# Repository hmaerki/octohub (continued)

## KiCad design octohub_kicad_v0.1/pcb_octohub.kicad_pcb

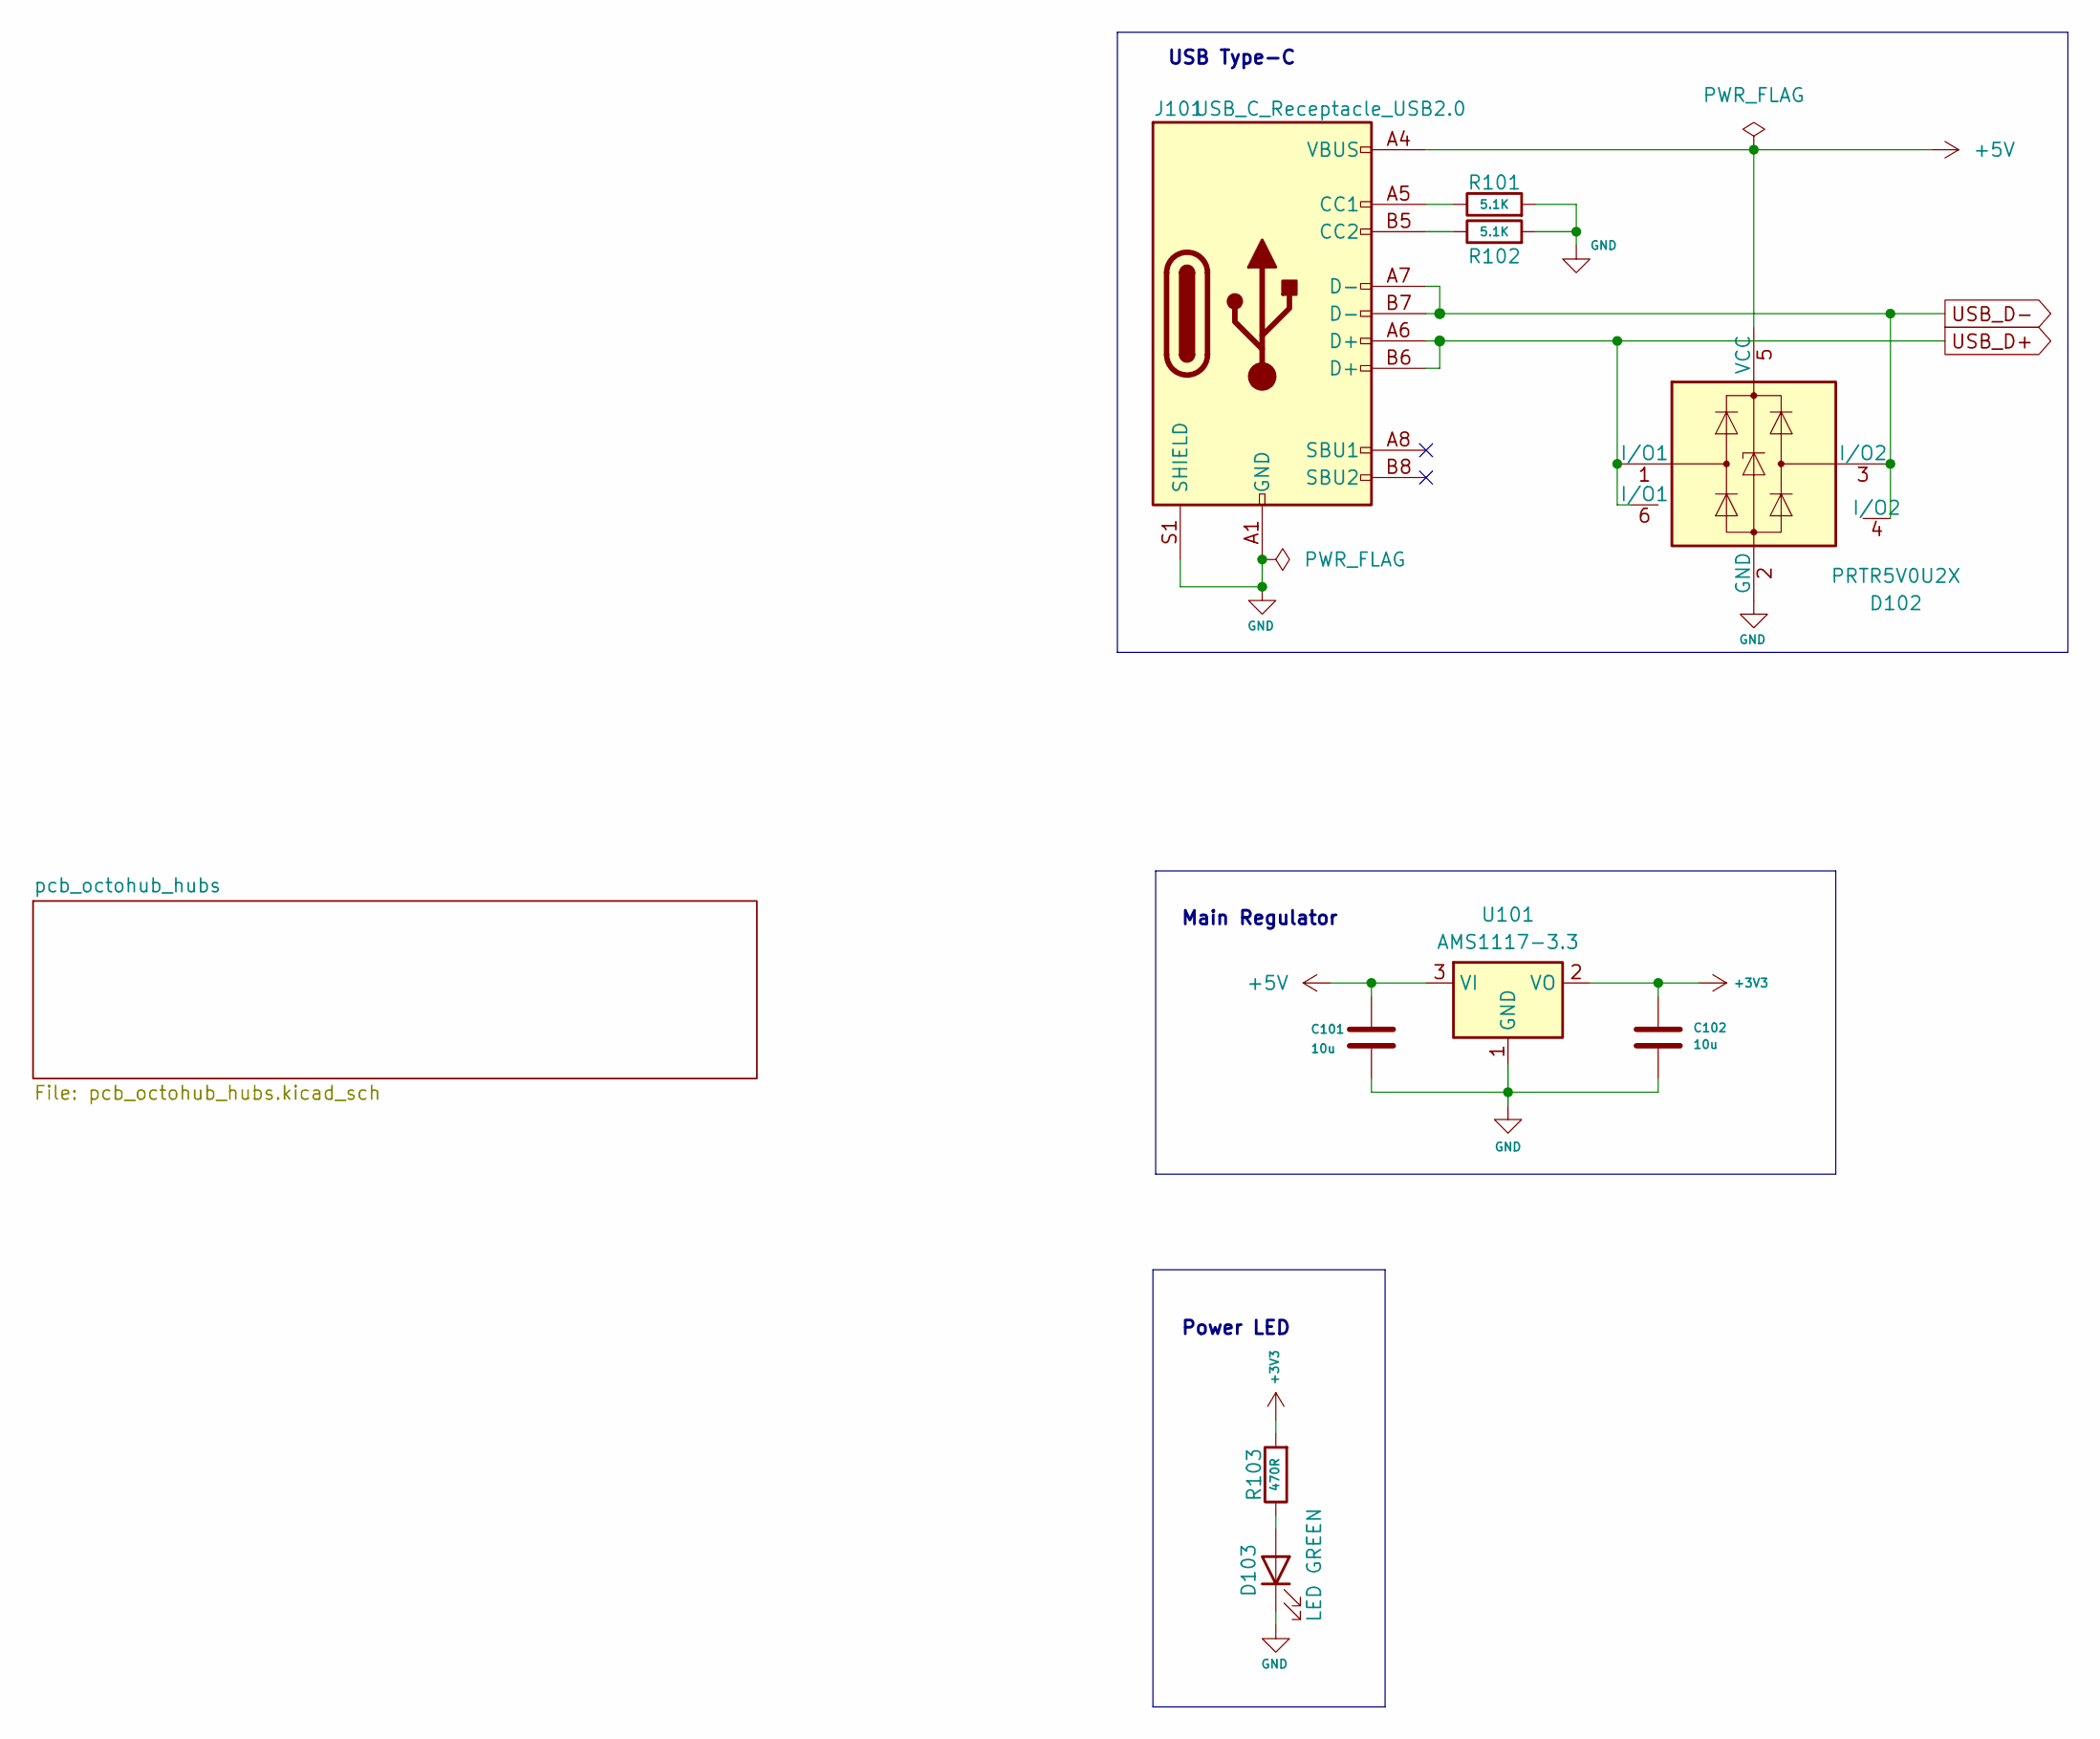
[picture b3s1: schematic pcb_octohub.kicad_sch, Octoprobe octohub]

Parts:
C101, C102: 10u; C_0603_1608Metric
D102: PRTR5V0U2X; Texas_USON-6_1x1.45mm_P0.5mm_SMD; JLC C2937001
D103: LED GREEN; LED_0603_1608Metric; JLC C2297
J101: USB_C_Receptacle_USB2.0; USB_C_Receptacle_Palconn_UTC16-G; JLC C165948
R101, R102: 5.1K; R_0402_1005Metric_Pad0.72x0.64mm_HandSolder
R103: 470R; R_0402_1005Metric_Pad0.72x0.64mm_HandSolder
U101: AMS1117-3.3; SOT-223-3_TabPin2; JLC C6186

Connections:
+3V3: C102.1, R103.2, U101.2 (VO); also elsewhere on the board
+5V: C101.1, D102.5 (VCC), J101.A4 (VBUS), J101.A9 (VBUS), J101.B4 (VBUS), J101.B9 (VBUS), U101.3 (VI); also elsewhere on the board
GND: C101.2, C102.2, D102.2 (GND), D103.1 (K), J101.A1 (GND), J101.A12 (GND), J101.B1 (GND), J101.B12 (GND), J101.S1 (SHIELD), R101.2, R102.2, U101.1 (GND); also elsewhere on the board
unnamed: D103.2 (A), R103.1
unnamed: J101.A5 (CC1), R101.1
unnamed: J101.B5 (CC2), R102.1
USB_D+: D102.1 (I/O1), D102.6 (I/O1), J101.A6 (D+), J101.B6 (D+); also elsewhere on the board
USB_D-: D102.3 (I/O2), D102.4 (I/O2), J101.A7 (D-), J101.B7 (D-); also elsewhere on the board

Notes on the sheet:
USB Type-C
Power LED
Main Regulator

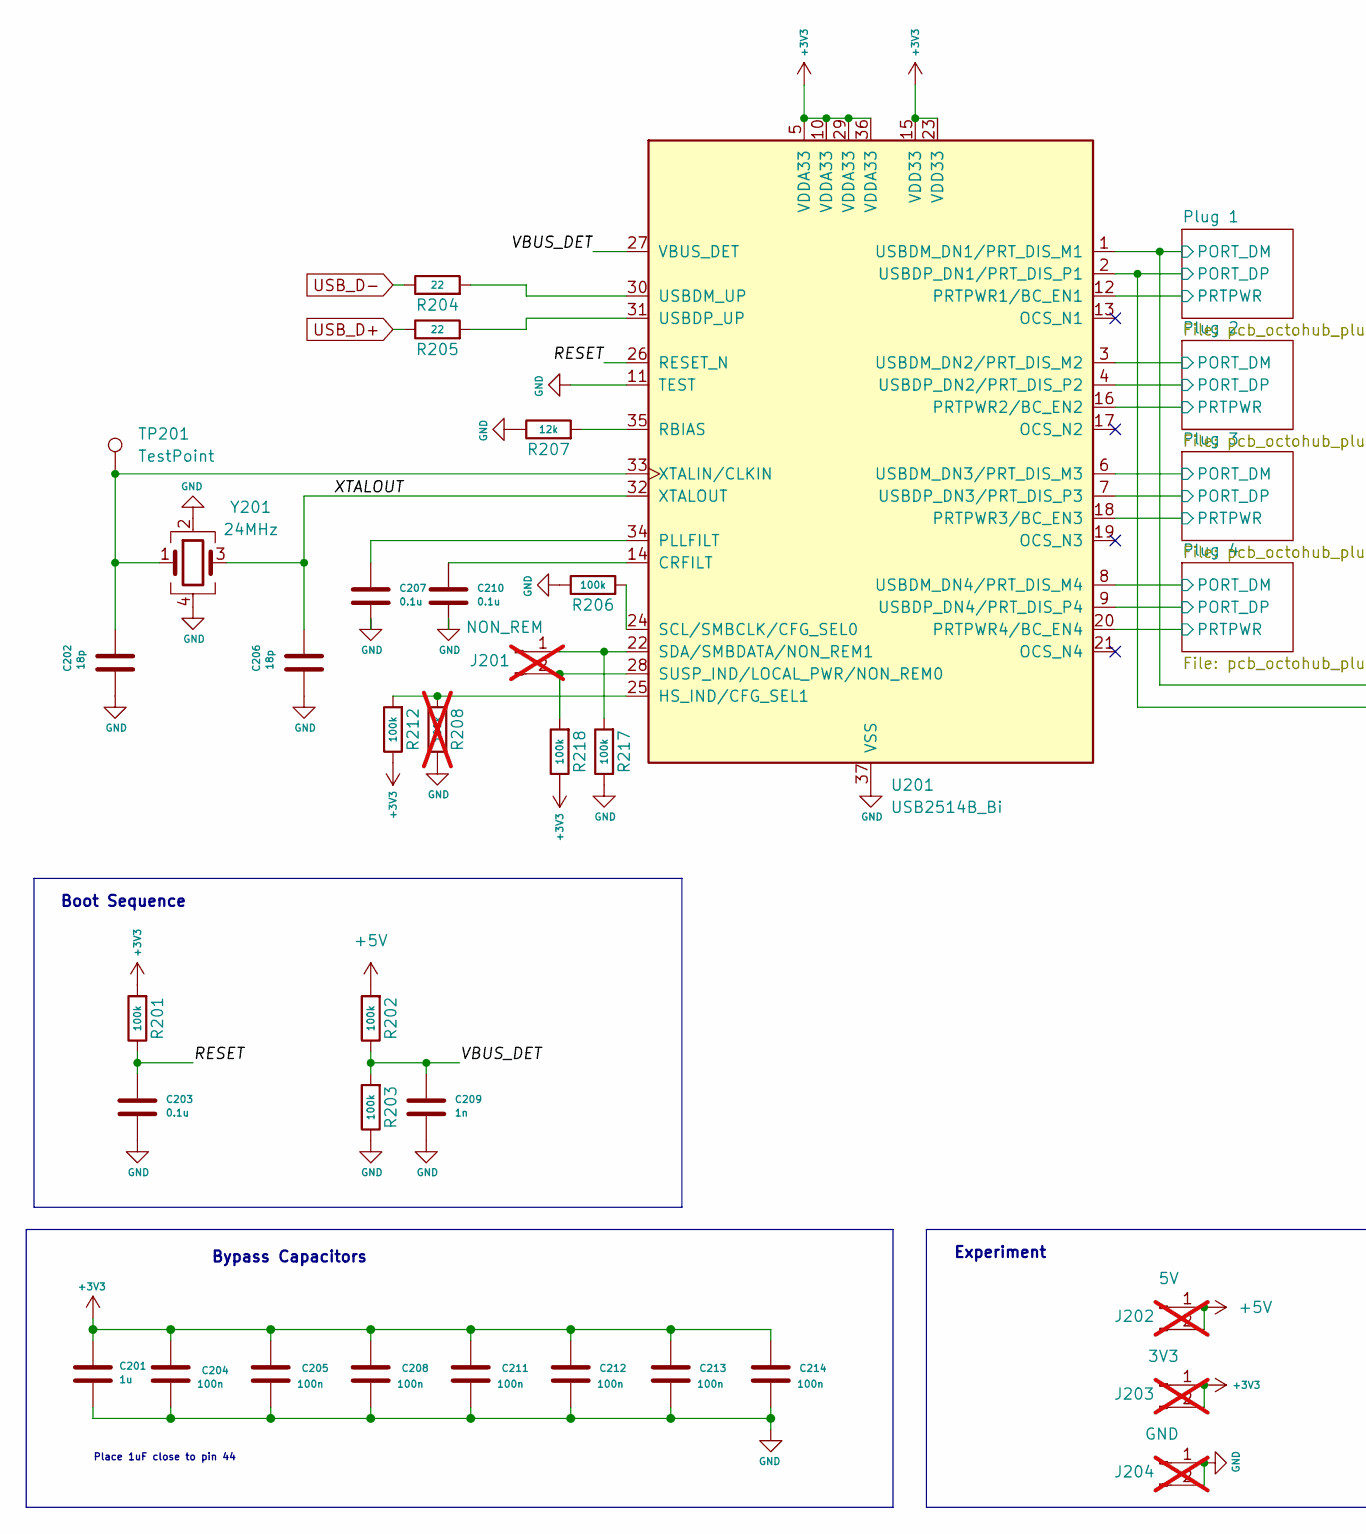
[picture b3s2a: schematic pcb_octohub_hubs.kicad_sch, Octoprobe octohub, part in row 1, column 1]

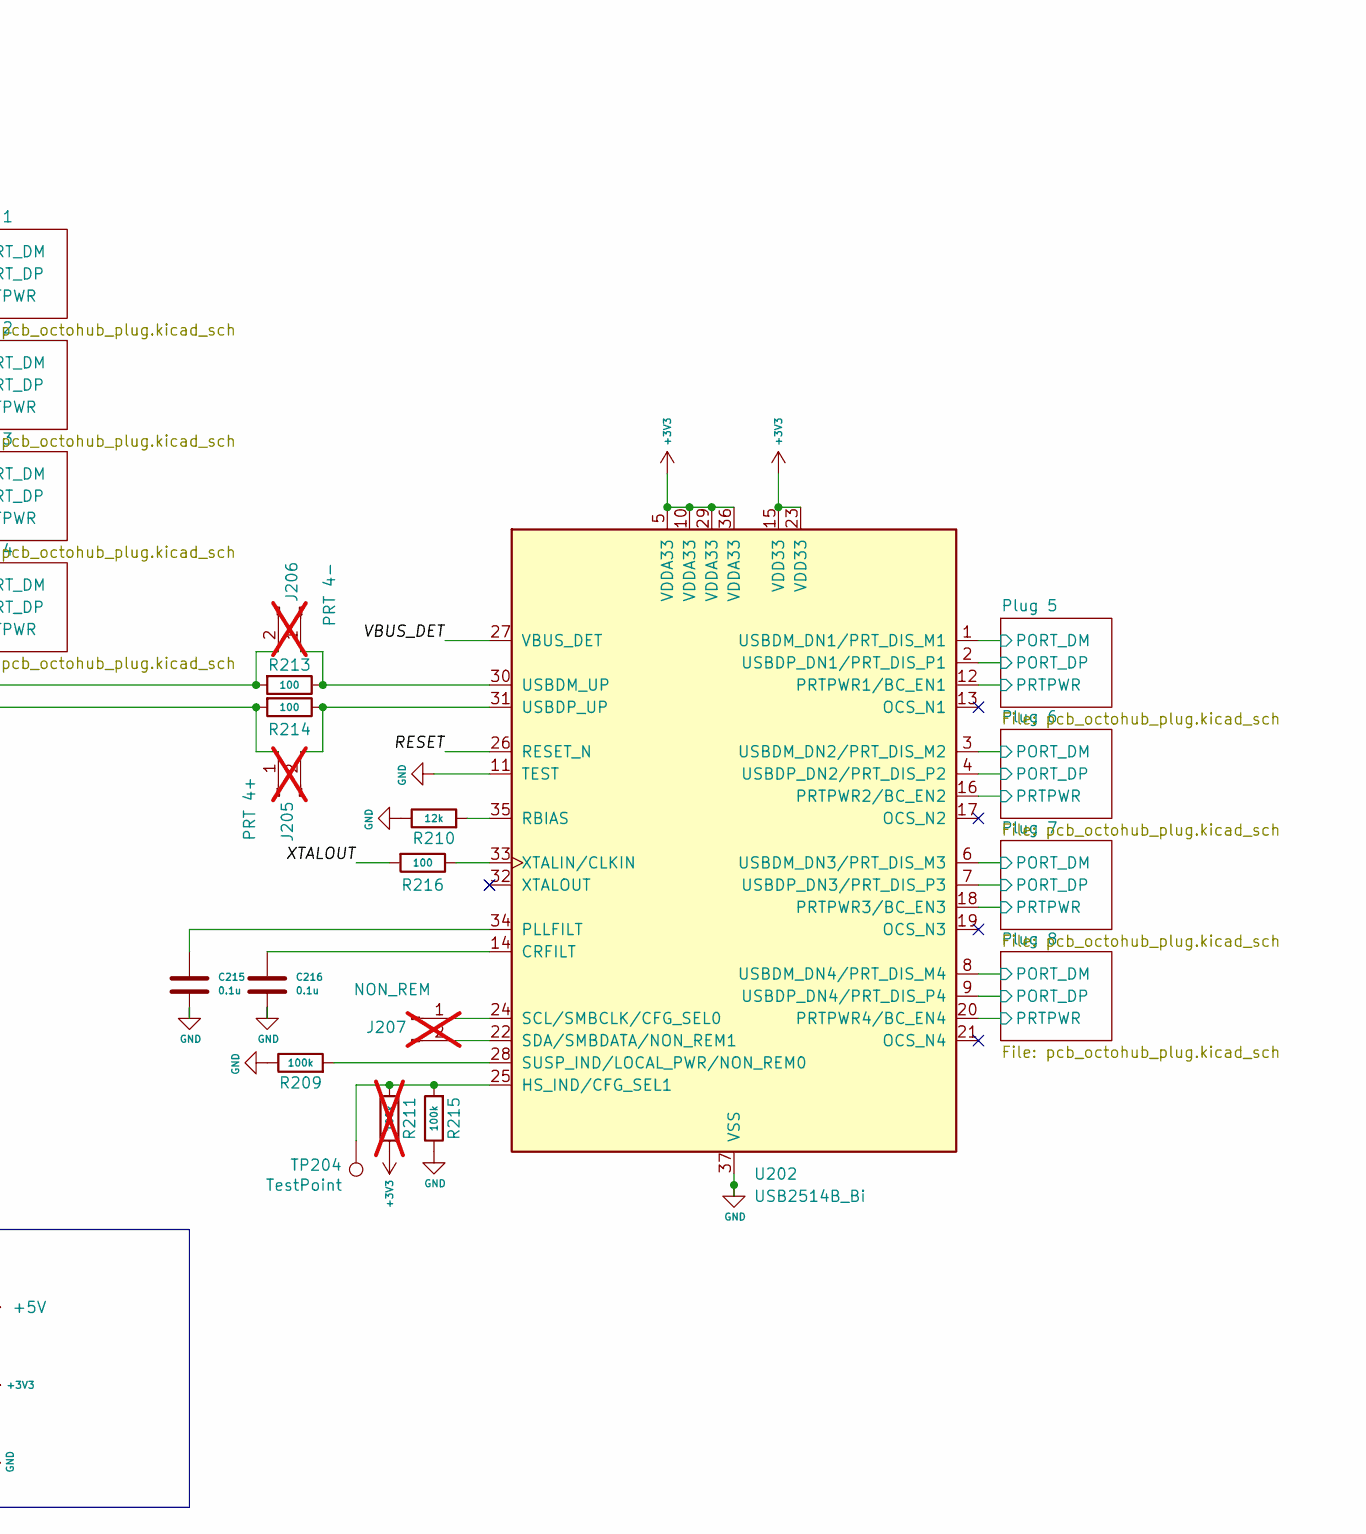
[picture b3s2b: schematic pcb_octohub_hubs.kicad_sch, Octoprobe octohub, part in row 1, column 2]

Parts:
C201: 1u; C_0402_1005Metric_Pad0.74x0.62mm_HandSolder
C202, C206: 18p; C_0805_2012Metric; JLC C1797
C203, C207, C210, C215, C216: 0.1u; C_0603_1608Metric
C204, C205, C208, C211, C212, C213, C214: 100n; C_0402_1005Metric_Pad0.74x0.62mm_HandSolder
C209: 1n; C_0603_1608Metric
J201, J207: NON_REM; PinHeader_1x02_P2.54mm_Vertical; not fitted
J202: 5V; PinHeader_1x02_P2.54mm_Vertical; not fitted
J203: 3V3; PinHeader_1x02_P2.54mm_Vertical; not fitted
J204: GND; PinHeader_1x02_P2.54mm_Vertical; not fitted
J205: PRT 4+; PinHeader_1x02_P2.54mm_Vertical; not fitted
J206: PRT 4-; PinHeader_1x02_P2.54mm_Vertical; not fitted
R201, R202, R203, R206, R209, R212, R215, R217, R218: 100k; R_0402_1005Metric_Pad0.72x0.64mm_HandSolder
R204, R205: 22; R_0402_1005Metric_Pad0.72x0.64mm_HandSolder
R207, R210: 12k; R_0402_1005Metric_Pad0.72x0.64mm_HandSolder
R208, R211: 100k; R_0402_1005Metric_Pad0.72x0.64mm_HandSolder; not fitted
R213, R214, R216: 100; R_0402_1005Metric_Pad0.72x0.64mm_HandSolder
TP201, TP204: TestPoint; TestPoint_Pad_1.0x1.0mm
U201, U202: USB2514B_Bi; Texas_RHH0036C_VQFN-36-1EP_6x6mm_P0.5mm_EP4.4x4.4mm_Thermal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; JLC C16251
Y201: 24MHz; Crystal_SMD_3225-4Pin_3.2x2.5mm; JLC C70590

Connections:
+3V3: C201.1, C204.1, C205.1, C208.1, C211.1, C212.1, C213.1, C214.1, J203.1, J203.2, R201.2, R211.1, R212.1, R218.1, U201.5 (VDDA33), U201.10 (VDDA33), U201.15 (VDD33), U201.23 (VDD33), U201.29 (VDDA33), U201.36 (VDDA33), U202.5 (VDDA33), U202.10 (VDDA33), U202.15 (VDD33), U202.23 (VDD33), U202.29 (VDDA33), U202.36 (VDDA33); also elsewhere on the board
+5V: J202.1, J202.2, R202.2; also elsewhere on the board
/pcb_octohub_hubs/Plug 1/PORT_DM: J206.2, R213.2, U201.1 (USBDM_DN1/PRT_DIS_M1); also elsewhere on the board
/pcb_octohub_hubs/Plug 1/PORT_DP: J205.1, R214.2, U201.2 (USBDP_DN1/PRT_DIS_P1); also elsewhere on the board
/pcb_octohub_hubs/Plug 1/PRTPWR: U201.12 (PRTPWR1/BC_EN1); also elsewhere on the board
/pcb_octohub_hubs/Plug 2/PORT_DM: U201.3 (USBDM_DN2/PRT_DIS_M2); also elsewhere on the board
/pcb_octohub_hubs/Plug 2/PORT_DP: U201.4 (USBDP_DN2/PRT_DIS_P2); also elsewhere on the board
/pcb_octohub_hubs/Plug 2/PRTPWR: U201.16 (PRTPWR2/BC_EN2); also elsewhere on the board
/pcb_octohub_hubs/Plug 3/PORT_DM: U201.6 (USBDM_DN3/PRT_DIS_M3); also elsewhere on the board
/pcb_octohub_hubs/Plug 3/PORT_DP: U201.7 (USBDP_DN3/PRT_DIS_P3); also elsewhere on the board
/pcb_octohub_hubs/Plug 3/PRTPWR: U201.18 (PRTPWR3/BC_EN3); also elsewhere on the board
/pcb_octohub_hubs/Plug 4/PORT_DM: U201.8 (USBDM_DN4/PRT_DIS_M4); also elsewhere on the board
/pcb_octohub_hubs/Plug 4/PORT_DP: U201.9 (USBDP_DN4/PRT_DIS_P4); also elsewhere on the board
/pcb_octohub_hubs/Plug 4/PRTPWR: U201.20 (PRTPWR4/BC_EN4); also elsewhere on the board
/pcb_octohub_hubs/Plug 5/PORT_DM: U202.1 (USBDM_DN1/PRT_DIS_M1); also elsewhere on the board
/pcb_octohub_hubs/Plug 5/PORT_DP: U202.2 (USBDP_DN1/PRT_DIS_P1); also elsewhere on the board
/pcb_octohub_hubs/Plug 5/PRTPWR: U202.12 (PRTPWR1/BC_EN1); also elsewhere on the board
/pcb_octohub_hubs/Plug 6/PORT_DM: U202.3 (USBDM_DN2/PRT_DIS_M2); also elsewhere on the board
/pcb_octohub_hubs/Plug 6/PORT_DP: U202.4 (USBDP_DN2/PRT_DIS_P2); also elsewhere on the board
/pcb_octohub_hubs/Plug 6/PRTPWR: U202.16 (PRTPWR2/BC_EN2); also elsewhere on the board
/pcb_octohub_hubs/Plug 7/PORT_DM: U202.6 (USBDM_DN3/PRT_DIS_M3); also elsewhere on the board
/pcb_octohub_hubs/Plug 7/PORT_DP: U202.7 (USBDP_DN3/PRT_DIS_P3); also elsewhere on the board
/pcb_octohub_hubs/Plug 7/PRTPWR: U202.18 (PRTPWR3/BC_EN3); also elsewhere on the board
/pcb_octohub_hubs/Plug 8/PORT_DM: U202.8 (USBDM_DN4/PRT_DIS_M4); also elsewhere on the board
/pcb_octohub_hubs/Plug 8/PORT_DP: U202.9 (USBDP_DN4/PRT_DIS_P4); also elsewhere on the board
/pcb_octohub_hubs/Plug 8/PRTPWR: U202.20 (PRTPWR4/BC_EN4); also elsewhere on the board
/pcb_octohub_hubs/RESET: C203.1, R201.1, U201.26 (RESET_N), U202.26 (RESET_N)
/pcb_octohub_hubs/VBUS_DET: C209.1, R202.1, R203.2, U201.27 (VBUS_DET), U202.27 (VBUS_DET)
/pcb_octohub_hubs/XTALOUT: C206.1, R216.2, U201.32 (XTALOUT), Y201.3
GND: C201.2, C202.2, C203.2, C204.2, C205.2, C206.2, C207.2, C208.2, C209.2, C210.2, C211.2, C212.2, C213.2, C214.2, C215.2, C216.2, J204.1, J204.2, R203.1, R206.1, R207.1, R208.1, R209.1, R210.1, R215.1, R217.1, U201.11 (TEST), U201.37 (VSS), U202.11 (TEST), U202.37 (VSS), Y201.2, Y201.4; also elsewhere on the board
unnamed: J201.1, R217.2, U201.22 (SDA/SMBDATA/NON_REM1)
unnamed: J201.2, R218.2, U201.28 (SUSP_IND/LOCAL_PWR/NON_REM0)
unnamed: J205.2, R214.1, U202.31 (USBDP_UP)
unnamed: J206.1, R213.1, U202.30 (USBDM_UP)
unnamed: J207.1, U202.24 (SCL/SMBCLK/CFG_SEL0)
unnamed: J207.2, U202.22 (SDA/SMBDATA/NON_REM1)
unnamed: C210.1, U201.14 (CRFILT)
unnamed: R208.2, R212.2, U201.25 (HS_IND/CFG_SEL1)
unnamed: C207.1, U201.34 (PLLFILT)
unnamed: R207.2, U201.35 (RBIAS)
unnamed: R206.2, U201.24 (SCL/SMBCLK/CFG_SEL0)
unnamed: R204.2, U201.30 (USBDM_UP)
unnamed: R205.2, U201.31 (USBDP_UP)
unnamed: C202.1, TP201.1, U201.33 (XTALIN/CLKIN), Y201.1
unnamed: C216.1, U202.14 (CRFILT)
unnamed: R211.2, R215.2, TP204.1, U202.25 (HS_IND/CFG_SEL1)
unnamed: C215.1, U202.34 (PLLFILT)
unnamed: R210.2, U202.35 (RBIAS)
unnamed: R209.2, U202.28 (SUSP_IND/LOCAL_PWR/NON_REM0)
unnamed: R216.1, U202.33 (XTALIN/CLKIN)
USB_D+: R205.1; also elsewhere on the board
USB_D-: R204.1; also elsewhere on the board

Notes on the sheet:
Place 1uF close to pin 44
Experiment
Bypass Capacitors
Boot Sequence

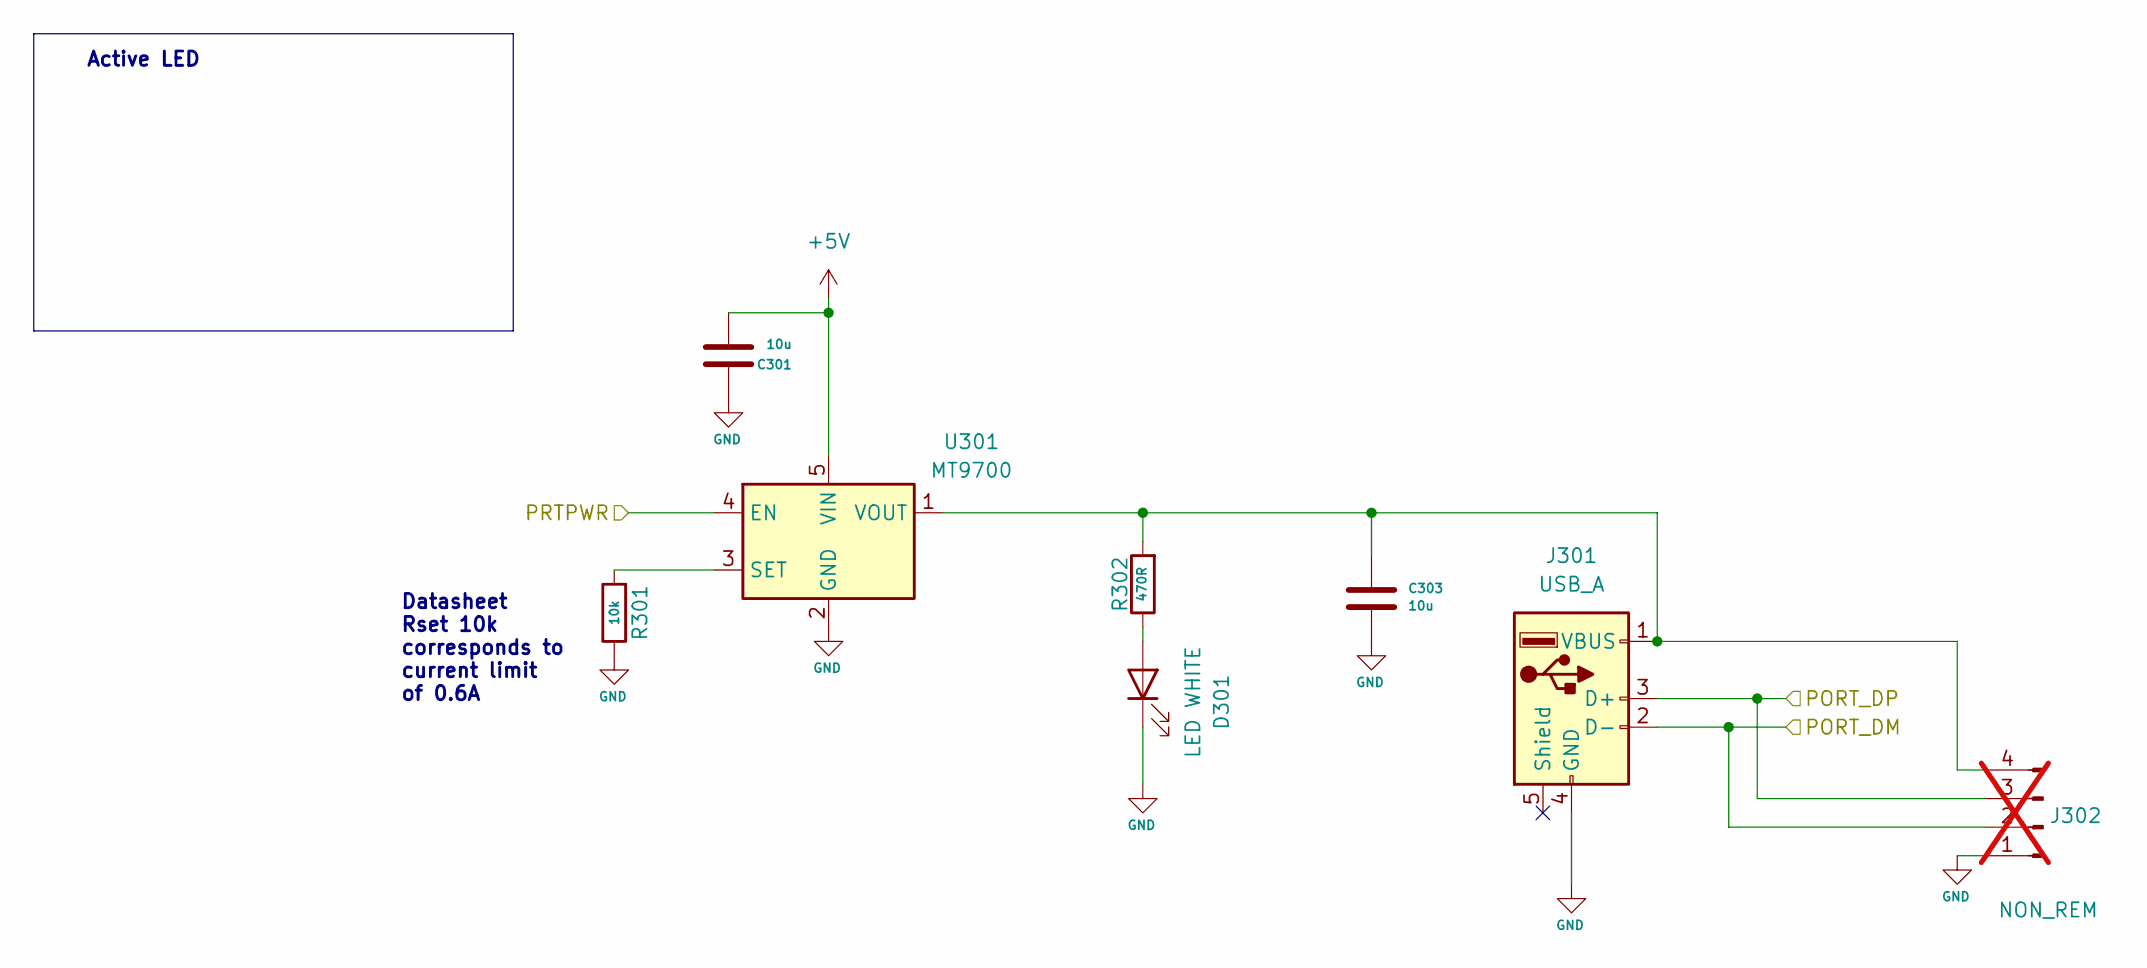
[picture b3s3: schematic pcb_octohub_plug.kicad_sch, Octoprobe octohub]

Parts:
C301, C303: 10u; C_0603_1608Metric
D301: LED WHITE; LED_0603_1608Metric; JLC C2290
J301: USB_A; USB_A_Molex_105057_Vertical; JLC C456015
J302: NON_REM; PinHeader_1x04_P2.54mm_Vertical; not fitted
R301: 10k; R_0402_1005Metric_Pad0.72x0.64mm_HandSolder
R302: 470R; R_0402_1005Metric_Pad0.72x0.64mm_HandSolder
U301: MT9700; SOT-23-5; JLC C89855

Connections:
+5V: C301.2, U301.5 (VIN); also elsewhere on the board
/pcb_octohub_hubs/Plug 1/PORT_DM: J301.2 (D-), J302.2; also elsewhere on the board
/pcb_octohub_hubs/Plug 1/PORT_DP: J301.3 (D+), J302.3; also elsewhere on the board
/pcb_octohub_hubs/Plug 1/PRTPWR: U301.4 (EN); also elsewhere on the board
GND: C301.1, C303.2, D301.1 (K), J301.4 (GND), J302.1, R301.1, U301.2 (GND); also elsewhere on the board
unnamed: D301.2 (A), R302.1
unnamed: C303.1, J301.1 (VBUS), J302.4, R302.2, U301.1 (VOUT)
unnamed: R301.2, U301.3 (SET)

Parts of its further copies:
C401, C403, C501, C503, C601, C603, C701, C703, C801, C803, C901, C903, C1001, C1003: 10u; C_0603_1608Metric
D401, D501, D601, D701, D801, D901, D1001: LED WHITE; LED_0603_1608Metric; JLC C2290
J401, J501, J601, J701, J801, J901, J1001: USB_A; USB_A_Molex_105057_Vertical; JLC C456015
J402, J502, J602, J702, J802, J902, J1002: NON_REM; PinHeader_1x04_P2.54mm_Vertical; not fitted
R401, R501, R601, R701, R801, R901, R1001: 10k; R_0402_1005Metric_Pad0.72x0.64mm_HandSolder
R402, R502, R602, R702, R802, R902, R1002: 470R; R_0402_1005Metric_Pad0.72x0.64mm_HandSolder
U401, U501, U601, U701, U801, U901, U1001: MT9700; SOT-23-5; JLC C89855

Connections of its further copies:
+5V: C401.2, C501.2, C601.2, C701.2, C801.2, C901.2, C1001.2, U401.5 (VIN), U501.5 (VIN), U601.5 (VIN), U701.5 (VIN), U801.5 (VIN), U901.5 (VIN), U1001.5 (VIN); also elsewhere on the board
/pcb_octohub_hubs/Plug 2/PORT_DM: J401.2 (D-), J402.2; also elsewhere on the board
/pcb_octohub_hubs/Plug 2/PORT_DP: J401.3 (D+), J402.3; also elsewhere on the board
/pcb_octohub_hubs/Plug 2/PRTPWR: U401.4 (EN); also elsewhere on the board
/pcb_octohub_hubs/Plug 3/PORT_DM: J501.2 (D-), J502.2; also elsewhere on the board
/pcb_octohub_hubs/Plug 3/PORT_DP: J501.3 (D+), J502.3; also elsewhere on the board
/pcb_octohub_hubs/Plug 3/PRTPWR: U501.4 (EN); also elsewhere on the board
/pcb_octohub_hubs/Plug 4/PORT_DM: J601.2 (D-), J602.2; also elsewhere on the board
/pcb_octohub_hubs/Plug 4/PORT_DP: J601.3 (D+), J602.3; also elsewhere on the board
/pcb_octohub_hubs/Plug 4/PRTPWR: U601.4 (EN); also elsewhere on the board
/pcb_octohub_hubs/Plug 5/PORT_DM: J701.2 (D-), J702.2; also elsewhere on the board
/pcb_octohub_hubs/Plug 5/PORT_DP: J701.3 (D+), J702.3; also elsewhere on the board
/pcb_octohub_hubs/Plug 5/PRTPWR: U701.4 (EN); also elsewhere on the board
/pcb_octohub_hubs/Plug 6/PORT_DM: J801.2 (D-), J802.2; also elsewhere on the board
/pcb_octohub_hubs/Plug 6/PORT_DP: J801.3 (D+), J802.3; also elsewhere on the board
/pcb_octohub_hubs/Plug 6/PRTPWR: U801.4 (EN); also elsewhere on the board
/pcb_octohub_hubs/Plug 7/PORT_DM: J901.2 (D-), J902.2; also elsewhere on the board
/pcb_octohub_hubs/Plug 7/PORT_DP: J901.3 (D+), J902.3; also elsewhere on the board
/pcb_octohub_hubs/Plug 7/PRTPWR: U901.4 (EN); also elsewhere on the board
/pcb_octohub_hubs/Plug 8/PORT_DM: J1001.2 (D-), J1002.2; also elsewhere on the board
/pcb_octohub_hubs/Plug 8/PORT_DP: J1001.3 (D+), J1002.3; also elsewhere on the board
/pcb_octohub_hubs/Plug 8/PRTPWR: U1001.4 (EN); also elsewhere on the board
GND: C401.1, C403.2, C501.1, C503.2, C601.1, C603.2, C701.1, C703.2, C801.1, C803.2, C901.1, C903.2, C1001.1, C1003.2, D401.1 (K), D501.1 (K), D601.1 (K), D701.1 (K), D801.1 (K), D901.1 (K), D1001.1 (K), J401.4 (GND), J402.1, J501.4 (GND), J502.1, J601.4 (GND), J602.1, J701.4 (GND), J702.1, J801.4 (GND), J802.1, J901.4 (GND), J902.1, J1001.4 (GND), J1002.1, R401.1, R501.1, R601.1, R701.1, R801.1, R901.1, R1001.1, U401.2 (GND), U501.2 (GND), U601.2 (GND), U701.2 (GND), U801.2 (GND), U901.2 (GND), U1001.2 (GND); also elsewhere on the board
unnamed: D401.2 (A), R402.1
unnamed: D501.2 (A), R502.1
unnamed: D601.2 (A), R602.1
unnamed: D701.2 (A), R702.1
unnamed: D801.2 (A), R802.1
unnamed: D901.2 (A), R902.1
unnamed: D1001.2 (A), R1002.1
unnamed: C403.1, J401.1 (VBUS), J402.4, R402.2, U401.1 (VOUT)
unnamed: C503.1, J501.1 (VBUS), J502.4, R502.2, U501.1 (VOUT)
unnamed: C603.1, J601.1 (VBUS), J602.4, R602.2, U601.1 (VOUT)
unnamed: C703.1, J701.1 (VBUS), J702.4, R702.2, U701.1 (VOUT)
unnamed: C803.1, J801.1 (VBUS), J802.4, R802.2, U801.1 (VOUT)
unnamed: C903.1, J901.1 (VBUS), J902.4, R902.2, U901.1 (VOUT)
unnamed: C1003.1, J1001.1 (VBUS), J1002.4, R1002.2, U1001.1 (VOUT)
unnamed: R401.2, U401.3 (SET)
unnamed: R501.2, U501.3 (SET)
unnamed: R601.2, U601.3 (SET)
unnamed: R701.2, U701.3 (SET)
unnamed: R801.2, U801.3 (SET)
unnamed: R901.2, U901.3 (SET)
unnamed: R1001.2, U1001.3 (SET)

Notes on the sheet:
Active LED
Datasheet Rset 10k corresponds to current limit of 0.6A

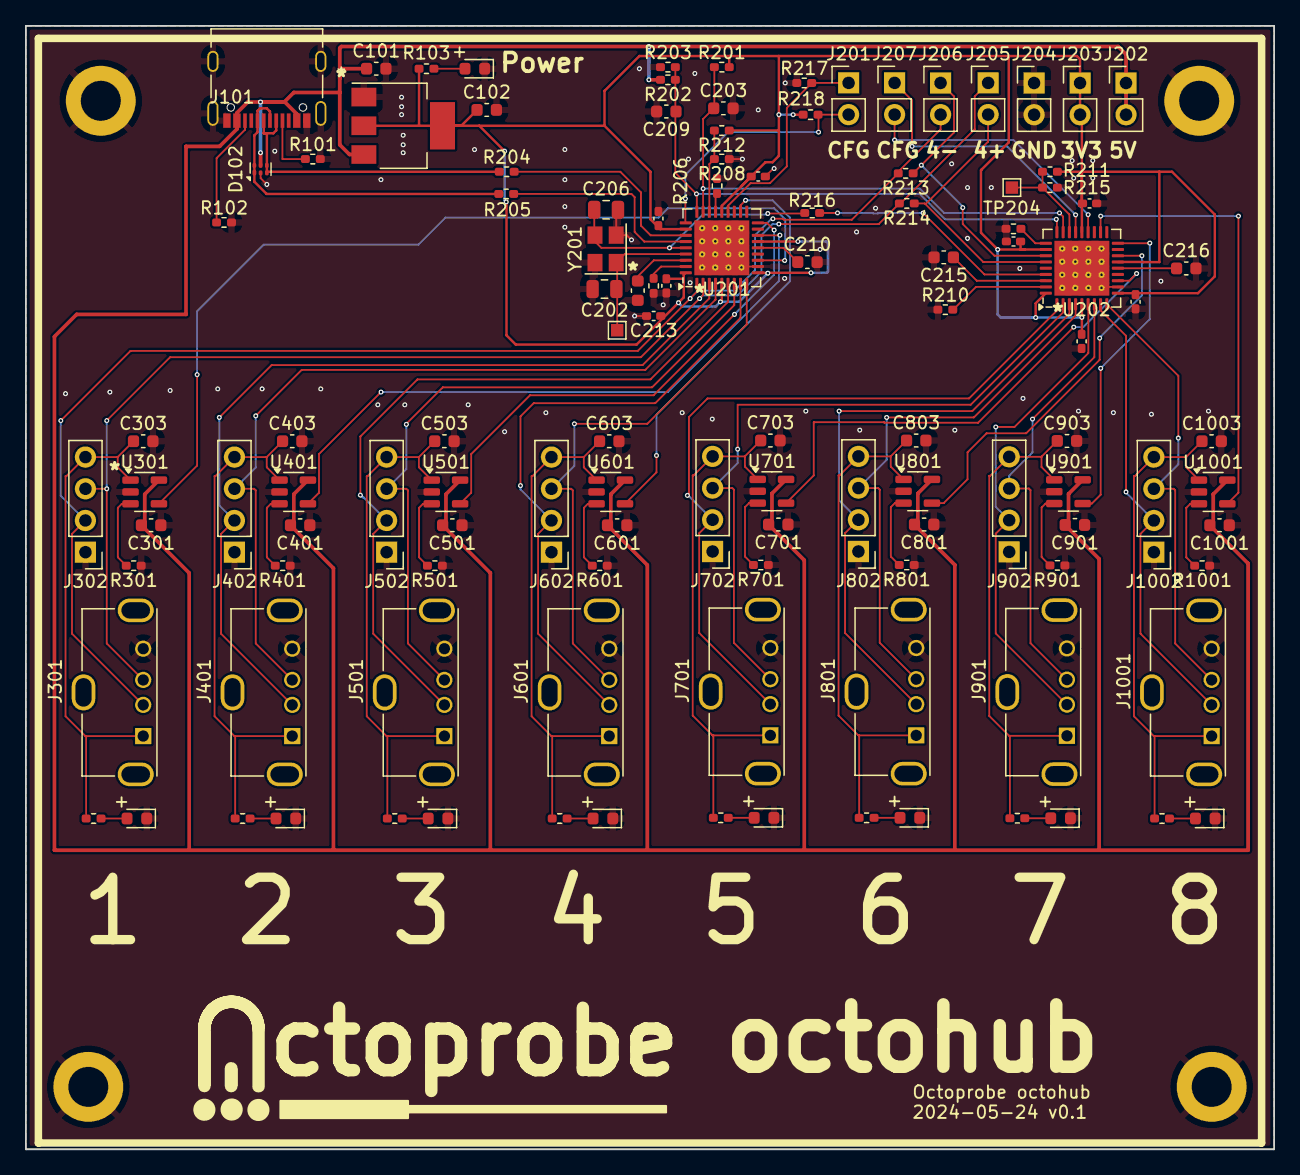
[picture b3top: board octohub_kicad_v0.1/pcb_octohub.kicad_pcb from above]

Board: 2 copper layers, 100.0 x 90.0 mm, 123 parts (0 on the bottom side), 79 nets.

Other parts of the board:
H101, H102, H103, H104: octoprobe_MountingHole; MountingHole_3.2mm_M3_DIN965_Pad

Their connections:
GND: H101.1, H102.1, H103.1, H104.1; also elsewhere on the board

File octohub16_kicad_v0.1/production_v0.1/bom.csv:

Designator,Footprint,Quantity,Value,LCSC Part #
"C1001, C1003, C101, C102, C301, C303, C401, C403, C501, C503, C601, C603, C701, C703, C801, C803, C901, C903",0603,18,10u,
C201,0402,1,1u,
"C202, C206",0805,2,18p,C1797
"C203, C207, C210, C215, C216",0603,5,0.1u,
"C204, C205, C208, C211, C212, C213, C214",0402,7,100n,
C209,0603,1,1n,
"D1001, D301, D401, D501, D601, D701, D801, D901",0603,8,LED WHITE,C2290
D102,Texas_USON-6_1x1.45mm_P0.5mm_SMD,1,PRTR5V0U2X,C2937001
D103,0603,1,LED GREEN,C2297
"H101, H102, H103, H104",MountingHole_3.2mm_M3_DIN965_Pad,4,octoprobe_MountingHole,
"J1001, J301, J401, J501, J601, J701, J801, J901",USB_A_Molex_105057_Vertical,8,USB_A,C456015
J101,USB_C_Receptacle_Palconn_UTC16-G,1,USB_C_Receptacle_USB2.0,C165948
"R1001, R301, R401, R501, R601, R701, R801, R901",0402,8,10k,
"R1002, R103, R302, R402, R502, R602, R702, R802, R902",0402,9,470R,
"R101, R102",0402,2,5.1K,
"R201, R202, R203, R206, R209, R212, R215, R217, R218",0402,9,100k,
"R204, R205",0402,2,22,
"R207, R210",0402,2,12k,
"R213, R214, R216",0402,3,100,
"U1001, U301, U401, U501, U601, U701, U801, U901",SOT-23-5,8,MT9700,C89855
U101,SOT-223-3_TabPin2,1,AMS1117-3.3,C6186
"U201, U202",Texas_RHH0036C_VQFN-36-1EP_6x6mm_P0.5mm_EP4.4x4.4mm_ThermalVias,2,USB2514B_Bi,C16251
Y201,Crystal_SMD_3225-4Pin_3.2x2.5mm,1,24MHz,C70590

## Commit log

2024-05-24 octohub_kicad_v0.1
2024-05-25 experiment octohub16
2024-06-17 commissioning v0.1
2024-06-18 4 port hub. octohub_kicad_v0.2
2024-07-02 Ideas for v0.3
